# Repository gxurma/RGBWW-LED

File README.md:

# RGBWW-LED
An LED board using RGBWW with WS2805 driver

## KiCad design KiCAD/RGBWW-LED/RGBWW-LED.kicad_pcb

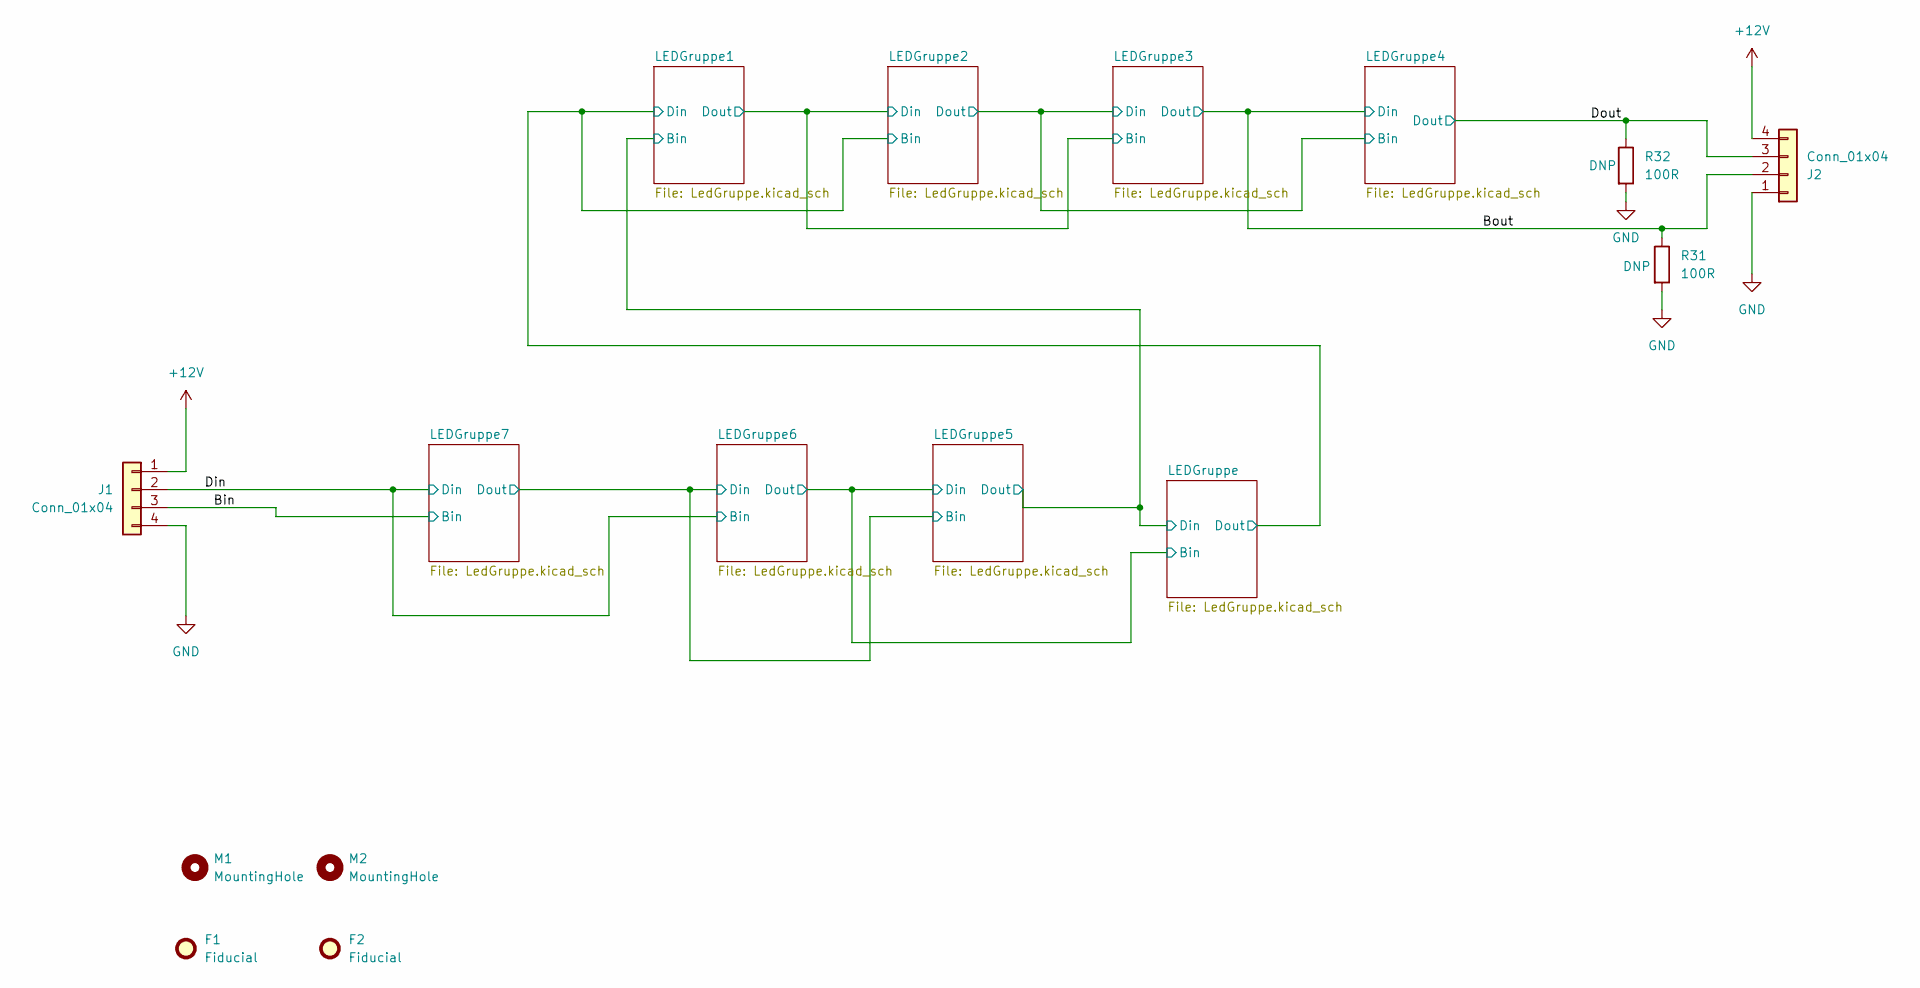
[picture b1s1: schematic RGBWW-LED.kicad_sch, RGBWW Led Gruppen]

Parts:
F1, F2: Fiducial; Fiducial_1mm_Mask2mm
J1, J2: Conn_01x04; PinHeader_1x04_P2.54mm_Horizontal
M1, M2: MountingHole; MountingHole_2.2mm_M2
R31, R32: 100R; R_0603_1608Metric_LedPrj

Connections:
+12V: J1.1, J2.4; also elsewhere on the board
/Bin: J1.3; also elsewhere on the board
/Bout: J2.2, R31.1; also elsewhere on the board
/Din: J1.2; also elsewhere on the board
/Dout: J2.3, R32.1; also elsewhere on the board
GND: J1.4, J2.1, R31.2, R32.2; also elsewhere on the board

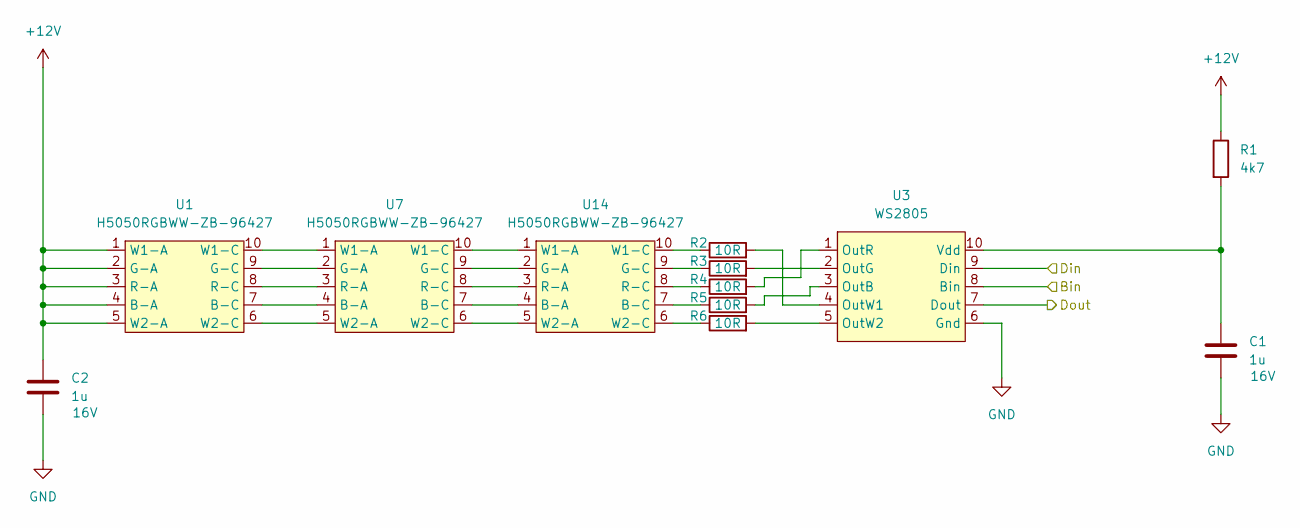
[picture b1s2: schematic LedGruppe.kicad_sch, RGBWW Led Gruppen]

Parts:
C1, C2: 1u; C_0603_1608Metric_LedPrj
R1: 4k7; R_0603_1608Metric_LedPrj
R2, R3, R4, R5, R6: 10R; R_0603_1608Metric_LedPrj
U1, U7, U14: H5050RGBWW-ZB-96427; LED_RGBWW_5050_10
U3: WS2805; SOIC-10_3.9x4.9mm_P1mm

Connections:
+12V: C2.1, R1.1, U1.1 (W1-A), U1.2 (G-A), U1.3 (R-A), U1.4 (B-A), U1.5 (W2-A); also elsewhere on the board
/LEDGruppe/Bin: U3.8 (Bin); also elsewhere on the board
/LEDGruppe/Din: U3.9 (Din); also elsewhere on the board
/LEDGruppe/Dout: U3.7 (Dout); also elsewhere on the board
GND: C1.2, C2.2, U3.6 (Gnd); also elsewhere on the board
unnamed: U1.7 (B-C), U7.4 (B-A)
unnamed: U1.9 (G-C), U7.2 (G-A)
unnamed: U1.8 (R-C), U7.3 (R-A)
unnamed: U1.10 (W1-C), U7.1 (W1-A)
unnamed: U1.6 (W2-C), U7.5 (W2-A)
unnamed: R5.2, U3.3 (OutB)
unnamed: R3.2, U3.2 (OutG)
unnamed: R4.2, U3.1 (OutR)
unnamed: R2.2, U3.4 (OutW1)
unnamed: R6.2, U3.5 (OutW2)
unnamed: C1.1, R1.2, U3.10 (Vdd)
unnamed: U7.7 (B-C), U14.4 (B-A)
unnamed: R5.1, U14.7 (B-C)
unnamed: U7.9 (G-C), U14.2 (G-A)
unnamed: R3.1, U14.9 (G-C)
unnamed: U7.8 (R-C), U14.3 (R-A)
unnamed: R4.1, U14.8 (R-C)
unnamed: U7.10 (W1-C), U14.1 (W1-A)
unnamed: R2.1, U14.10 (W1-C)
unnamed: U7.6 (W2-C), U14.5 (W2-A)
unnamed: R6.1, U14.6 (W2-C)

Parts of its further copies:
C3, C4, C5, C6, C7, C8, C9, C10, C11, C12, C13, C14, C15, C16: 1u; C_0603_1608Metric_LedPrj
R7, R8, R9, R10, R11, R13, R14, R15, R16, R17, R19, R20, R21, R22, R23, R25, R26, R27, R28, R29, R33, R34, R35, R36, R37, R39, R40, R41, R42, R43, R45, R46, R47, R48, R49: 10R; R_0603_1608Metric_LedPrj
R12, R18, R24, R30, R38, R44, R50: 4k7; R_0603_1608Metric_LedPrj
U2, U4, U5, U6, U9, U10, U11, U13, U15, U17, U18, U19, U21, U22, U23, U25, U26, U27, U29, U30, U31: H5050RGBWW-ZB-96427; LED_RGBWW_5050_10
U8, U12, U16, U20, U24, U28, U32: WS2805; SOIC-10_3.9x4.9mm_P1mm

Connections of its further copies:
+12V: C3.1, C5.1, C7.1, C9.1, C11.1, C13.1, C15.1, R12.1, R18.1, R24.1, R30.1, R38.1, R44.1, R50.1, U2.1 (W1-A), U2.2 (G-A), U2.3 (R-A), U2.4 (B-A), U2.5 (W2-A), U4.1 (W1-A), U4.2 (G-A), U4.3 (R-A), U4.4 (B-A), U4.5 (W2-A), U5.1 (W1-A), U5.2 (G-A), U5.3 (R-A), U5.4 (B-A), U5.5 (W2-A), U6.1 (W1-A), U6.2 (G-A), U6.3 (R-A), U6.4 (B-A), U6.5 (W2-A), U21.1 (W1-A), U21.2 (G-A), U21.3 (R-A), U21.4 (B-A), U21.5 (W2-A), U25.1 (W1-A), U25.2 (G-A), U25.3 (R-A), U25.4 (B-A), U25.5 (W2-A), U29.1 (W1-A), U29.2 (G-A), U29.3 (R-A), U29.4 (B-A), U29.5 (W2-A); also elsewhere on the board
/Bin: U32.8 (Bin); also elsewhere on the board
/Bout: U16.7 (Dout), U20.9 (Din); also elsewhere on the board
/Din: U28.8 (Bin), U32.9 (Din); also elsewhere on the board
/Dout: U20.7 (Dout); also elsewhere on the board
/LEDGruppe1/Dout: U8.7 (Dout), U12.9 (Din), U16.8 (Bin)
/LEDGruppe2/Dout: U12.7 (Dout), U16.9 (Din), U20.8 (Bin)
/LEDGruppe5/Bin: U24.8 (Bin), U28.9 (Din), U32.7 (Dout)
/LEDGruppe/Bin: U24.9 (Din), U28.7 (Dout); also elsewhere on the board
/LEDGruppe/Din: U8.8 (Bin), U24.7 (Dout); also elsewhere on the board
/LEDGruppe/Dout: U8.9 (Din), U12.8 (Bin); also elsewhere on the board
GND: C3.2, C4.2, C5.2, C6.2, C7.2, C8.2, C9.2, C10.2, C11.2, C12.2, C13.2, C14.2, C15.2, C16.2, U8.6 (Gnd), U12.6 (Gnd), U16.6 (Gnd), U20.6 (Gnd), U24.6 (Gnd), U28.6 (Gnd), U32.6 (Gnd); also elsewhere on the board
unnamed: U2.7 (B-C), U9.4 (B-A)
unnamed: U2.9 (G-C), U9.2 (G-A)
unnamed: U2.8 (R-C), U9.3 (R-A)
unnamed: U2.10 (W1-C), U9.1 (W1-A)
unnamed: U2.6 (W2-C), U9.5 (W2-A)
unnamed: R10.2, U8.3 (OutB)
unnamed: R8.2, U8.2 (OutG)
unnamed: R9.2, U8.1 (OutR)
unnamed: R7.2, U8.4 (OutW1)
unnamed: R11.2, U8.5 (OutW2)
unnamed: C4.1, R12.2, U8.10 (Vdd)
unnamed: U4.7 (B-C), U10.4 (B-A)
unnamed: U10.7 (B-C), U17.4 (B-A)
unnamed: U4.9 (G-C), U10.2 (G-A)
unnamed: U10.9 (G-C), U17.2 (G-A)
unnamed: U4.8 (R-C), U10.3 (R-A)
unnamed: U10.8 (R-C), U17.3 (R-A)
unnamed: U4.10 (W1-C), U10.1 (W1-A)
unnamed: U10.10 (W1-C), U17.1 (W1-A)
unnamed: U4.6 (W2-C), U10.5 (W2-A)
unnamed: U10.6 (W2-C), U17.5 (W2-A)
unnamed: U5.7 (B-C), U11.4 (B-A)
unnamed: U11.7 (B-C), U18.4 (B-A)
unnamed: U5.9 (G-C), U11.2 (G-A)
unnamed: U11.9 (G-C), U18.2 (G-A)
unnamed: U5.8 (R-C), U11.3 (R-A)
unnamed: U11.8 (R-C), U18.3 (R-A)
unnamed: U5.10 (W1-C), U11.1 (W1-A)
unnamed: U11.10 (W1-C), U18.1 (W1-A)
unnamed: U5.6 (W2-C), U11.5 (W2-A)
unnamed: U11.6 (W2-C), U18.5 (W2-A)
unnamed: R16.2, U12.3 (OutB)
unnamed: R14.2, U12.2 (OutG)
unnamed: R15.2, U12.1 (OutR)
unnamed: R13.2, U12.4 (OutW1)
unnamed: R17.2, U12.5 (OutW2)
unnamed: C6.1, R18.2, U12.10 (Vdd)
unnamed: U6.7 (B-C), U13.4 (B-A)
unnamed: U13.7 (B-C), U19.4 (B-A)
unnamed: U6.9 (G-C), U13.2 (G-A)
unnamed: U13.9 (G-C), U19.2 (G-A)
unnamed: U6.8 (R-C), U13.3 (R-A)
unnamed: U13.8 (R-C), U19.3 (R-A)
unnamed: U6.10 (W1-C), U13.1 (W1-A)
unnamed: U13.10 (W1-C), U19.1 (W1-A)
unnamed: U6.6 (W2-C), U13.5 (W2-A)
unnamed: U13.6 (W2-C), U19.5 (W2-A)
unnamed: U9.7 (B-C), U15.4 (B-A)
unnamed: R10.1, U15.7 (B-C)
unnamed: U9.9 (G-C), U15.2 (G-A)
unnamed: R8.1, U15.9 (G-C)
unnamed: U9.8 (R-C), U15.3 (R-A)
unnamed: R9.1, U15.8 (R-C)
unnamed: U9.10 (W1-C), U15.1 (W1-A)
unnamed: R7.1, U15.10 (W1-C)
unnamed: U9.6 (W2-C), U15.5 (W2-A)
unnamed: R11.1, U15.6 (W2-C)
unnamed: R22.2, U16.3 (OutB)
unnamed: R20.2, U16.2 (OutG)
unnamed: R21.2, U16.1 (OutR)
unnamed: R19.2, U16.4 (OutW1)
unnamed: R23.2, U16.5 (OutW2)
unnamed: C8.1, R24.2, U16.10 (Vdd)
unnamed: R16.1, U17.7 (B-C)
unnamed: R14.1, U17.9 (G-C)
unnamed: R15.1, U17.8 (R-C)
unnamed: R13.1, U17.10 (W1-C)
unnamed: R17.1, U17.6 (W2-C)
unnamed: R22.1, U18.7 (B-C)
unnamed: R20.1, U18.9 (G-C)
unnamed: R21.1, U18.8 (R-C)
unnamed: R19.1, U18.10 (W1-C)
unnamed: R23.1, U18.6 (W2-C)
unnamed: R28.1, U19.7 (B-C)
unnamed: R26.1, U19.9 (G-C)
unnamed: R27.1, U19.8 (R-C)
unnamed: R25.1, U19.10 (W1-C)
unnamed: R29.1, U19.6 (W2-C)
unnamed: R28.2, U20.3 (OutB)
unnamed: R26.2, U20.2 (OutG)
unnamed: R27.2, U20.1 (OutR)
unnamed: R25.2, U20.4 (OutW1)
unnamed: R29.2, U20.5 (OutW2)
unnamed: C10.1, R30.2, U20.10 (Vdd)
unnamed: U21.7 (B-C), U22.4 (B-A)
unnamed: U21.9 (G-C), U22.2 (G-A)
unnamed: U21.8 (R-C), U22.3 (R-A)
unnamed: U21.10 (W1-C), U22.1 (W1-A)
unnamed: U21.6 (W2-C), U22.5 (W2-A)
unnamed: U22.7 (B-C), U23.4 (B-A)
unnamed: U22.9 (G-C), U23.2 (G-A)
unnamed: U22.8 (R-C), U23.3 (R-A)
unnamed: U22.10 (W1-C), U23.1 (W1-A)
unnamed: U22.6 (W2-C), U23.5 (W2-A)
unnamed: R36.1, U23.7 (B-C)
unnamed: R34.1, U23.9 (G-C)
unnamed: R35.1, U23.8 (R-C)
unnamed: R33.1, U23.10 (W1-C)
unnamed: R37.1, U23.6 (W2-C)
unnamed: R36.2, U24.3 (OutB)
unnamed: R34.2, U24.2 (OutG)
unnamed: R35.2, U24.1 (OutR)
unnamed: R33.2, U24.4 (OutW1)
unnamed: R37.2, U24.5 (OutW2)
unnamed: C12.1, R38.2, U24.10 (Vdd)
unnamed: U25.7 (B-C), U26.4 (B-A)
unnamed: U25.9 (G-C), U26.2 (G-A)
unnamed: U25.8 (R-C), U26.3 (R-A)
unnamed: U25.10 (W1-C), U26.1 (W1-A)
unnamed: U25.6 (W2-C), U26.5 (W2-A)
unnamed: U26.7 (B-C), U27.4 (B-A)
unnamed: U26.9 (G-C), U27.2 (G-A)
unnamed: U26.8 (R-C), U27.3 (R-A)
unnamed: U26.10 (W1-C), U27.1 (W1-A)
unnamed: U26.6 (W2-C), U27.5 (W2-A)
unnamed: R42.1, U27.7 (B-C)
unnamed: R40.1, U27.9 (G-C)
unnamed: R41.1, U27.8 (R-C)
unnamed: R39.1, U27.10 (W1-C)
unnamed: R43.1, U27.6 (W2-C)
unnamed: R42.2, U28.3 (OutB)
unnamed: R40.2, U28.2 (OutG)
unnamed: R41.2, U28.1 (OutR)
unnamed: R39.2, U28.4 (OutW1)
unnamed: R43.2, U28.5 (OutW2)
unnamed: C14.1, R44.2, U28.10 (Vdd)
unnamed: U29.7 (B-C), U30.4 (B-A)
unnamed: U29.9 (G-C), U30.2 (G-A)
unnamed: U29.8 (R-C), U30.3 (R-A)
unnamed: U29.10 (W1-C), U30.1 (W1-A)
unnamed: U29.6 (W2-C), U30.5 (W2-A)
unnamed: U30.7 (B-C), U31.4 (B-A)
unnamed: U30.9 (G-C), U31.2 (G-A)
unnamed: U30.8 (R-C), U31.3 (R-A)
unnamed: U30.10 (W1-C), U31.1 (W1-A)
unnamed: U30.6 (W2-C), U31.5 (W2-A)
unnamed: R48.1, U31.7 (B-C)
unnamed: R46.1, U31.9 (G-C)
unnamed: R47.1, U31.8 (R-C)
unnamed: R45.1, U31.10 (W1-C)
unnamed: R49.1, U31.6 (W2-C)
unnamed: R48.2, U32.3 (OutB)
unnamed: R46.2, U32.2 (OutG)
unnamed: R47.2, U32.1 (OutR)
unnamed: R45.2, U32.4 (OutW1)
unnamed: R49.2, U32.5 (OutW2)
unnamed: C16.1, R50.2, U32.10 (Vdd)

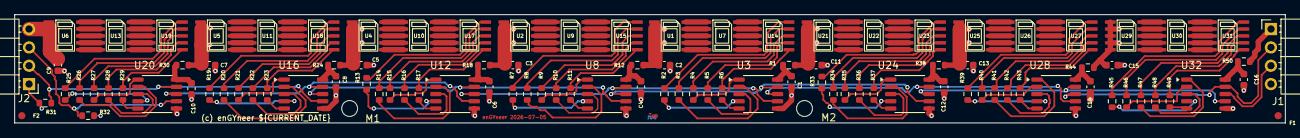
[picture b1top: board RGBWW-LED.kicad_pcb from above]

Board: 2 copper layers, 176.0 x 15.0 mm, 104 parts (0 on the bottom side), 180 nets.

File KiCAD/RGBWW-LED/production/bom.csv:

Designator,Footprint,Quantity,Value,LCSC Part #
"C1, C10, C11, C12, C13, C14, C15, C16, C2, C3, C4, C5, C6, C7, C8, C9",0603,16,1u,
"J1, J2",PinHeader_1x04_P2.54mm_Horizontal,2,Conn_01x04,
"R1, R12, R18, R24, R30, R38, R44, R50",0603,8,4k7,
"R10, R11, R13, R14, R15, R16, R17, R19, R2, R20, R21, R22, R23, R25, R26, R27, R28, R29, R3, R33, R34, R35, R36, R37, R39, R4, R40, R41, R42, R43, R45, R46, R47, R48, R49, R5, R6, R7, R8, R9",0603,40,10R,
"R31, R32",0603,2,100R,
"U1, U10, U11, U13, U14, U15, U17, U18, U19, U2, U21, U22, U23, U25, U26, U27, U29, U30, U31, U4, U5, U6, U7, U9",LED_RGBWW_5050_10,24,H5050RGBWW-ZB-96427,
"U12, U16, U20, U24, U28, U3, U32, U8",SOIC-10_3.9x4.9mm_P1mm,8,WS2805,

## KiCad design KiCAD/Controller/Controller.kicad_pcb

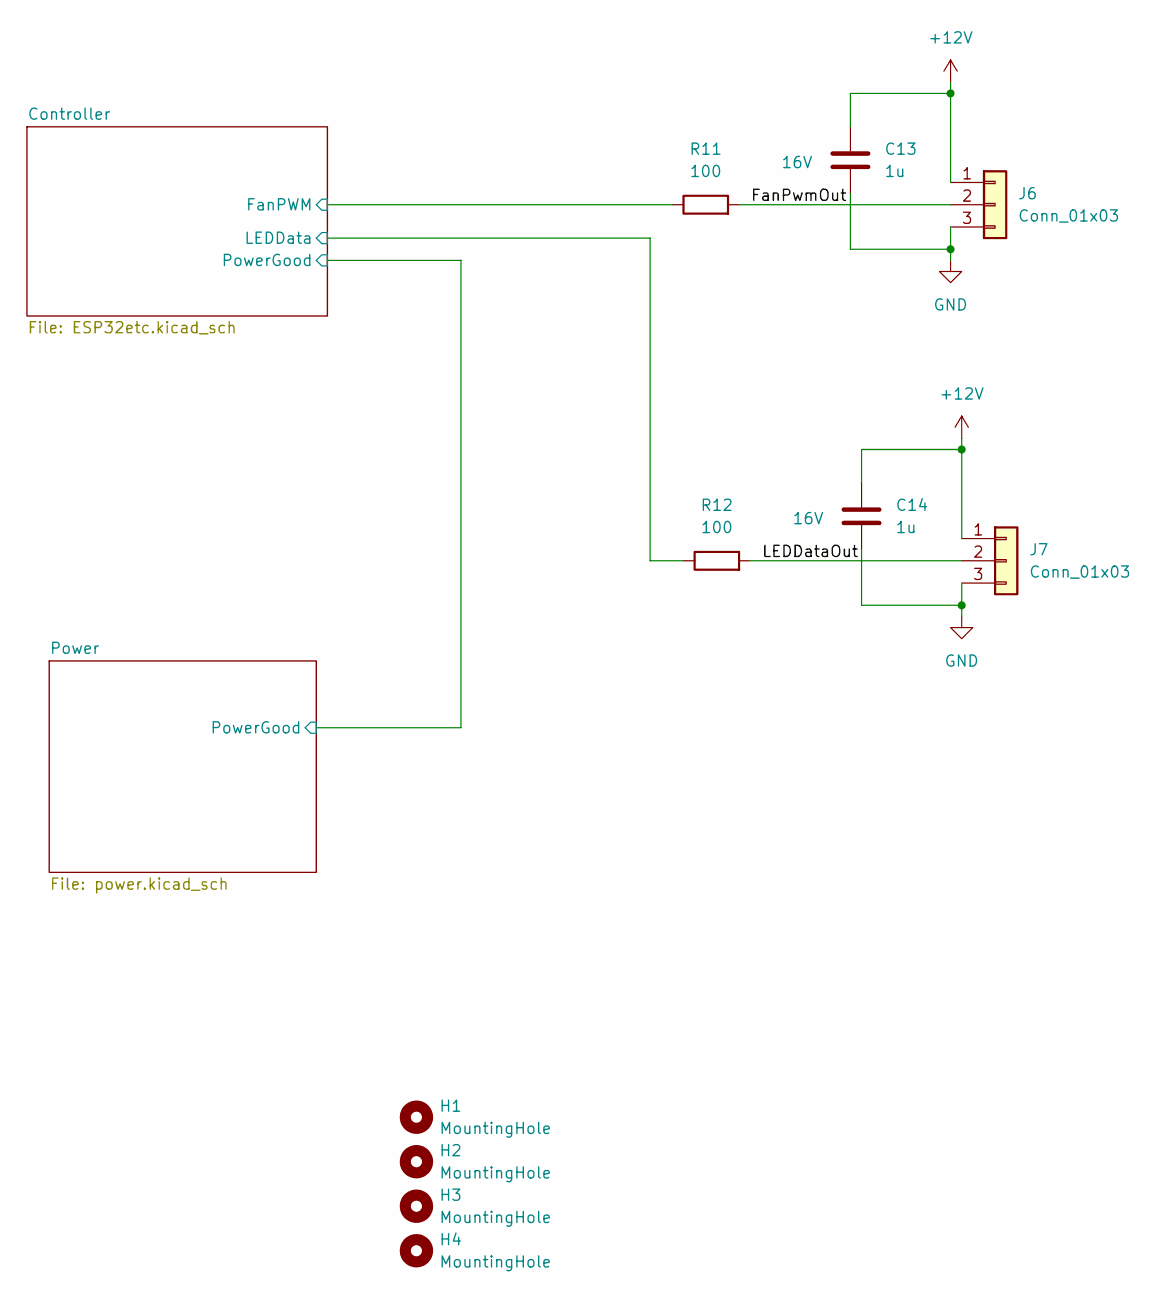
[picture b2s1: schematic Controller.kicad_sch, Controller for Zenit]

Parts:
C13, C14: 1u; C_0603_1608Metric; Manufacturer Part CL10A105KO8NNNC; JLCPCB C1592
H1, H2, H3, H4: MountingHole; MountingHole_3.2mm_M3
J6, J7: Conn_01x03; JST_XH_B3B-XH-A_1x03_P2.50mm_Vertical
R11, R12: 100; R_0603_1608Metric_LedPrj

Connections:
+12V: C13.1, C14.1, J6.1, J7.1; also elsewhere on the board
/Controller/FanPWM: R11.1; also elsewhere on the board
/Controller/LEDData: R12.1; also elsewhere on the board
/FanPwmOut: J6.2, R11.2
/LEDDataOut: J7.2, R12.2
GND: C13.2, C14.2, J6.3, J7.3; also elsewhere on the board

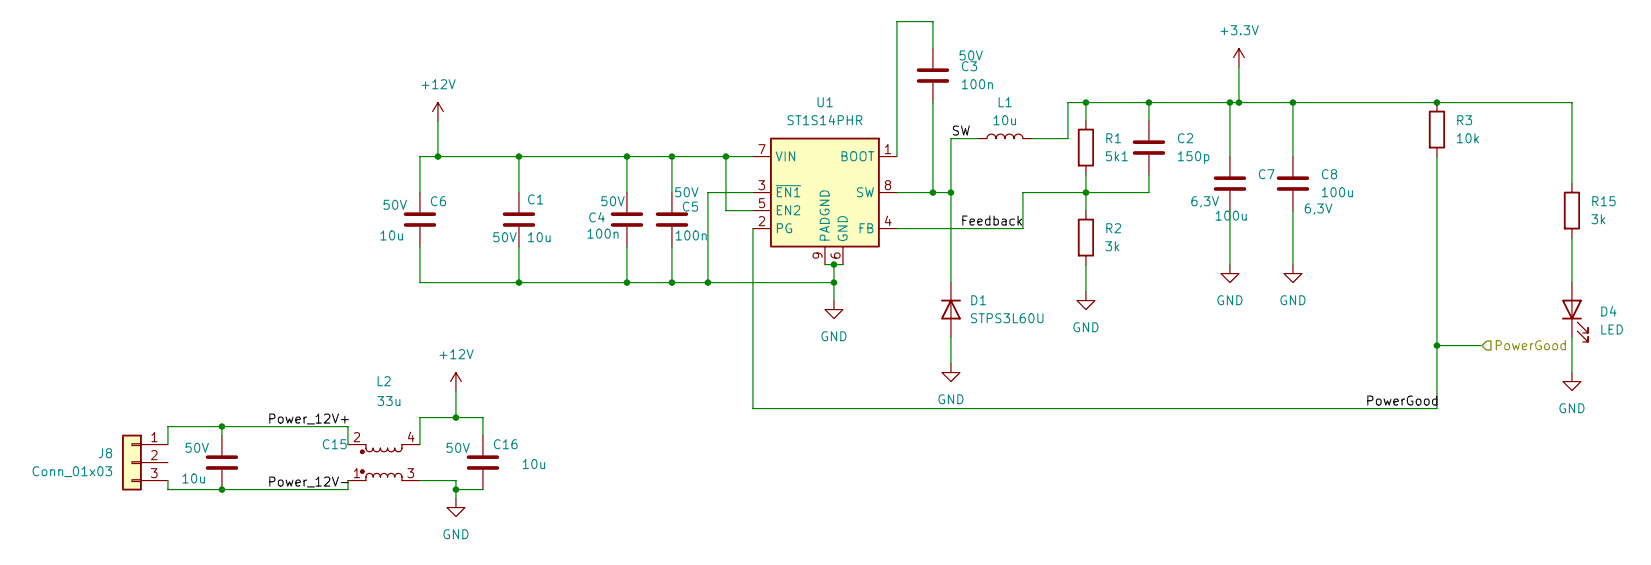
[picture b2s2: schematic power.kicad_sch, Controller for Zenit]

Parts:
C1, C6, C15, C16: 10u; C_1210_3225Metric; Manufacturer Part CL31A106KBHNNNE
C2: 150p; C_0603_1608Metric
C3, C4, C5: 100n; C_0603_1608Metric; Manufacturer Part CC0603KRX7R9BB104
C7, C8: 100u; C_1206_3216Metric; Manufacturer Part CL31A107MQHNNNE
D1: STPS3L60U; D_SMB_Handsoldering
D4: LED; LED_0603_1608Metric
J8: Conn_01x03; JST_XH_B3B-XH-A_1x03_P2.50mm_Vertical
L1: 10u; L_Wuerth_HCI-7050; Manufacturer Part 744314101
L2: 33u; L_CommonModeChoke_Bourns_SRF1260; Manufacturer Part SRF1260-330M
R1: 5k1; R_0603_1608Metric_LedPrj
R2, R15: 3k; R_0603_1608Metric_LedPrj
R3: 10k; R_0603_1608Metric_LedPrj
U1: ST1S14PHR; TI_SO-PowerPAD-8; Manufacturer Part ST1S14PHR

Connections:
+3.3V: C2.1, C7.1, C8.1, L1.2, R1.1, R3.1, R15.1; also elsewhere on the board
+12V: C1.1, C4.1, C5.1, C6.1, C16.1, L2.4, U1.5 (EN2), U1.7 (VIN); also elsewhere on the board
/Power/Feedback: C2.2, R1.2, R2.1, U1.4 (FB)
/Power/PowerGood: R3.2, U1.2 (PG); also elsewhere on the board
/Power/Power_12V+: C15.1, J8.1, L2.2
/Power/Power_12V-: C15.2, J8.3, L2.1
/Power/SW: C3.2, D1.1 (K), L1.1, U1.8 (SW)
GND: C1.2, C4.2, C5.2, C6.2, C7.2, C8.2, C16.2, D1.2 (A), D4.1 (K), L2.3, R2.2, U1.3 (~EN1), U1.6 (GND), U1.9 (PADGND); also elsewhere on the board
unnamed: D4.2 (A), R15.2
unnamed: C3.1, U1.1 (BOOT)

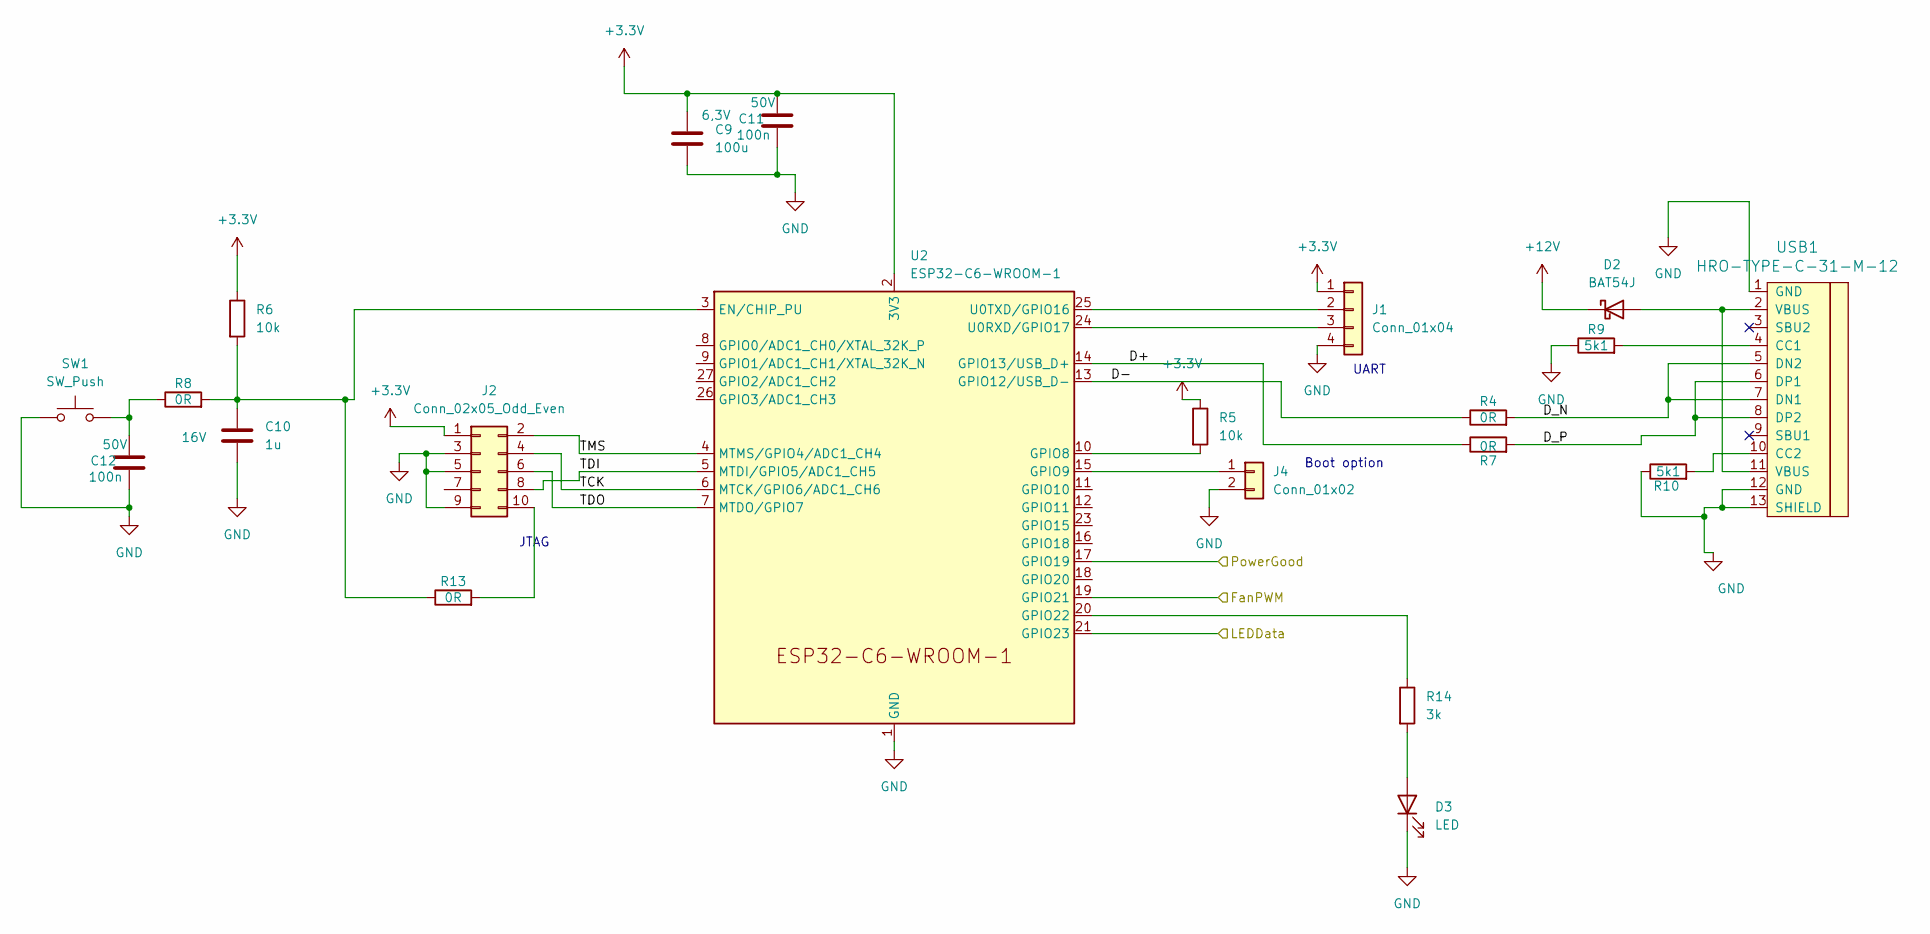
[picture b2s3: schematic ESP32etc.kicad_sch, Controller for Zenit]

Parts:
C9: 100u; C_1206_3216Metric; Manufacturer Part CL31A107MQHNNNE
C10: 1u; C_0603_1608Metric; Manufacturer Part CL10A105KO8NNNC; JLCPCB C1592
C11, C12: 100n; C_0603_1608Metric; Manufacturer Part CC0603KRX7R9BB104
D2: BAT54J; D_SOD-323F
D3: LED; LED_0603_1608Metric
J1: Conn_01x04; PinHeader_1x04_P2.54mm_Vertical_SMD_Pin1Left
J2: Conn_02x05_Odd_Even; PinHeader_2x05_P2.54mm_Vertical
J4: Conn_01x02; PinHeader_1x02_P2.54mm_Vertical_SMD_Pin1Left
R4, R7, R8, R13: 0R; R_0603_1608Metric_LedPrj
R5, R6: 10k; R_0603_1608Metric_LedPrj
R9, R10: 5k1; R_0603_1608Metric_LedPrj
R14: 3k; R_0603_1608Metric_LedPrj
SW1: SW_Push; SW_PUSH_6mm_H5mm
U2: ESP32-C6-WROOM-1
USB1: HRO-TYPE-C-31-M-12; HRO-TYPE-C-31-M-12-Assembly; LCSC C165948

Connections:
+3.3V: C9.1, C11.1, J1.1, J2.1, R5.1, R6.1, U2.2 (3V3); also elsewhere on the board
+12V: D2.1 (K); also elsewhere on the board
/Controller/D+: R7.1, U2.14 (GPIO13/USB_D+)
/Controller/D-: R4.1, U2.13 (GPIO12/USB_D-)
/Controller/D_N: R4.2, USB1.5 (DN2), USB1.7 (DN1)
/Controller/D_P: R7.2, USB1.6 (DP1), USB1.8 (DP2)
/Controller/FanPWM: U2.19 (GPIO21); also elsewhere on the board
/Controller/LEDData: U2.21 (GPIO23); also elsewhere on the board
/Controller/TCK: J2.4, U2.6 (MTCK/GPIO6/ADC1_CH6)
/Controller/TDI: J2.8, U2.5 (MTDI/GPIO5/ADC1_CH5)
/Controller/TDO: J2.6, U2.7 (MTDO/GPIO7)
/Controller/TMS: J2.2, U2.4 (MTMS/GPIO4/ADC1_CH4)
/Power/PowerGood: U2.17 (GPIO19); also elsewhere on the board
GND: C9.2, C10.2, C11.2, C12.2, D3.1 (K), J1.4, J2.3, J2.5, J2.9, J4.2, R9.1, R10.1, SW1.1, U2.1 (GND), U2.28 (GND), U2.29 (GND), USB1.1 (GND), USB1.12 (GND), USB1.13 (SHIELD); also elsewhere on the board
unnamed: C12.1, R8.1, SW1.2
unnamed: D2.2 (A), USB1.2 (VBUS), USB1.11 (VBUS)
unnamed: D3.2 (A), R14.2
unnamed: J1.2, U2.25 (U0TXD/GPIO16)
unnamed: J1.3, U2.24 (U0RXD/GPIO17)
unnamed: J2.10, R13.2
unnamed: J4.1, U2.15 (GPIO9)
unnamed: C10.1, R6.2, R8.2, R13.1, U2.3 (EN/CHIP_PU)
unnamed: R5.2, U2.10 (GPIO8)
unnamed: R14.1, U2.20 (GPIO22)
unnamed: R9.2, USB1.4 (CC1)
unnamed: R10.2, USB1.10 (CC2)

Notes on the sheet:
Boot option
JTAG
UART

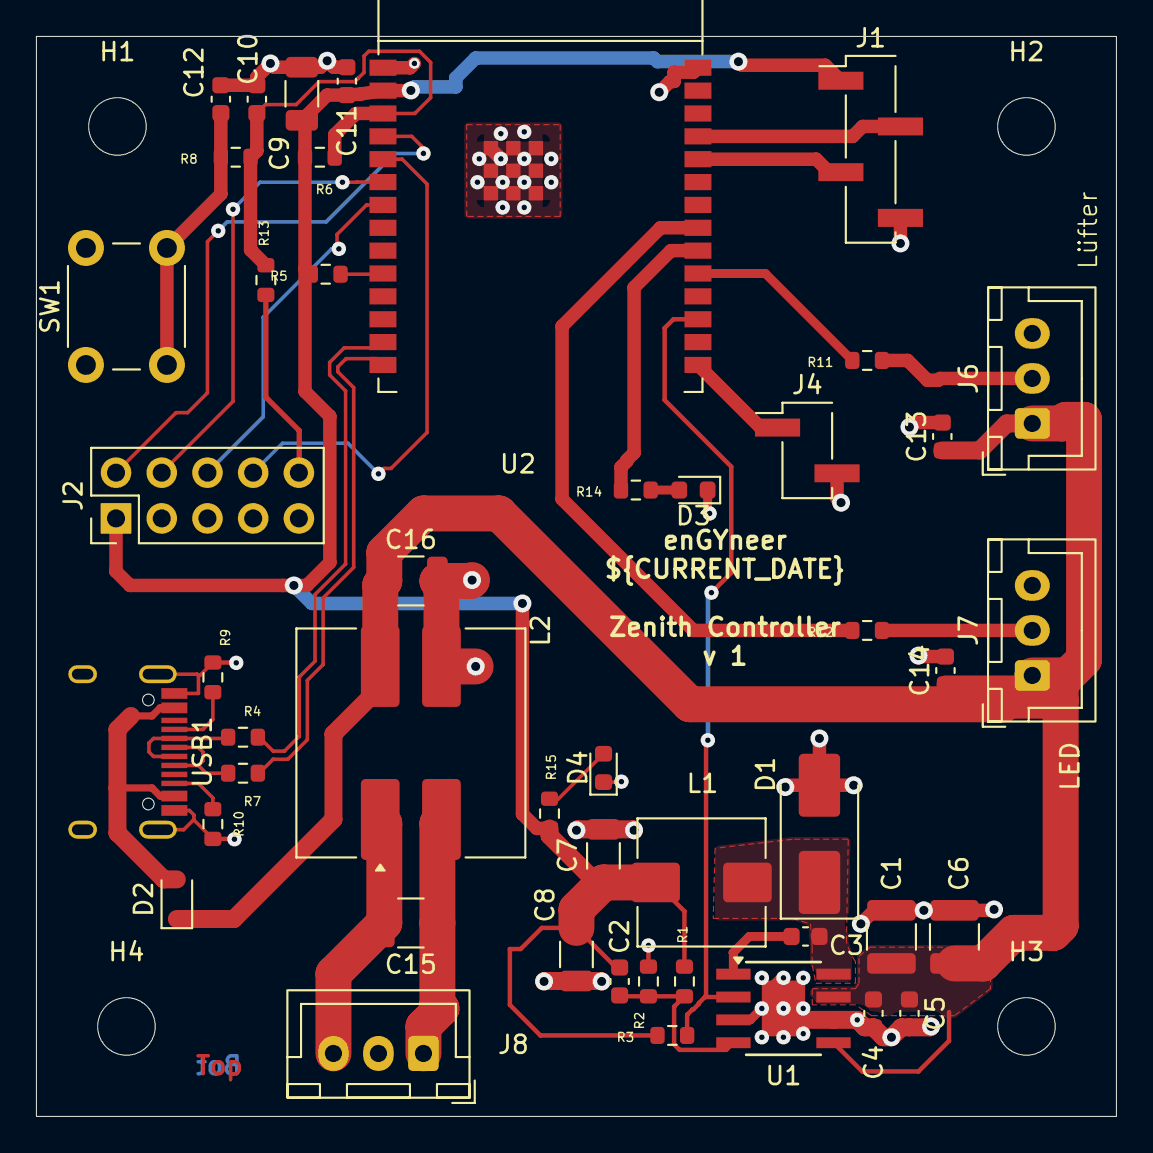
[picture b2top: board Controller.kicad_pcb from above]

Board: 2 copper layers, 60.0 x 60.0 mm, 51 parts (0 on the bottom side), 34 nets.

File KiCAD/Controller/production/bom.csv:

Designator,Footprint,Quantity,Value,LCSC Part #
"C1, C15, C16, C6",1210,4,10u,
"C10, C13, C14",0603,3,1u,
"C11, C12, C3, C4, C5",0603,5,100n,
C2,0603,1,150p,
"C7, C8, C9",1206,3,100u,
D1,D_SMB_Handsoldering,1,STPS3L60U,
D2,D_SOD-323F,1,BAT54J,
"D3, D4",0603,2,LED,
J1,PinHeader_1x04_P2.54mm_Vertical_SMD_Pin1Left,1,Conn_01x04,
J2,PinHeader_2x05_P2.54mm_Vertical,1,Conn_02x05_Odd_Even,
J4,PinHeader_1x02_P2.54mm_Vertical_SMD_Pin1Left,1,Conn_01x02,
"J6, J7, J8",JST_XH_B3B-XH-A_1x03_P2.50mm_Vertical,3,Conn_01x03,
L1,L_Wuerth_HCI-7050,1,10u,
L2,L_CommonModeChoke_Bourns_SRF1260,1,33u,
"R1, R10, R9",0603,3,5k1,
"R11, R12",0603,2,100,
"R13, R4, R7, R8",0603,4,0R,
"R14, R15, R2",0603,3,3k,
"R3, R5, R6",0603,3,10k,
SW1,SW_PUSH_6mm_H5mm,1,SW_Push,
U1,TI_SO-PowerPAD-8,1,ST1S14PHR,
U2,ESP32-C6-WROOM-1,1,ESP32-C6-WROOM-1,
USB1,HRO-TYPE-C-31-M-12-Assembly,1,HRO-TYPE-C-31-M-12,C165948

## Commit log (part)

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2026-06-26 first commit, added structure and some pdf
2026-06-26 added RGBWW LED symbol
2026-06-29 added Ledgruppe
